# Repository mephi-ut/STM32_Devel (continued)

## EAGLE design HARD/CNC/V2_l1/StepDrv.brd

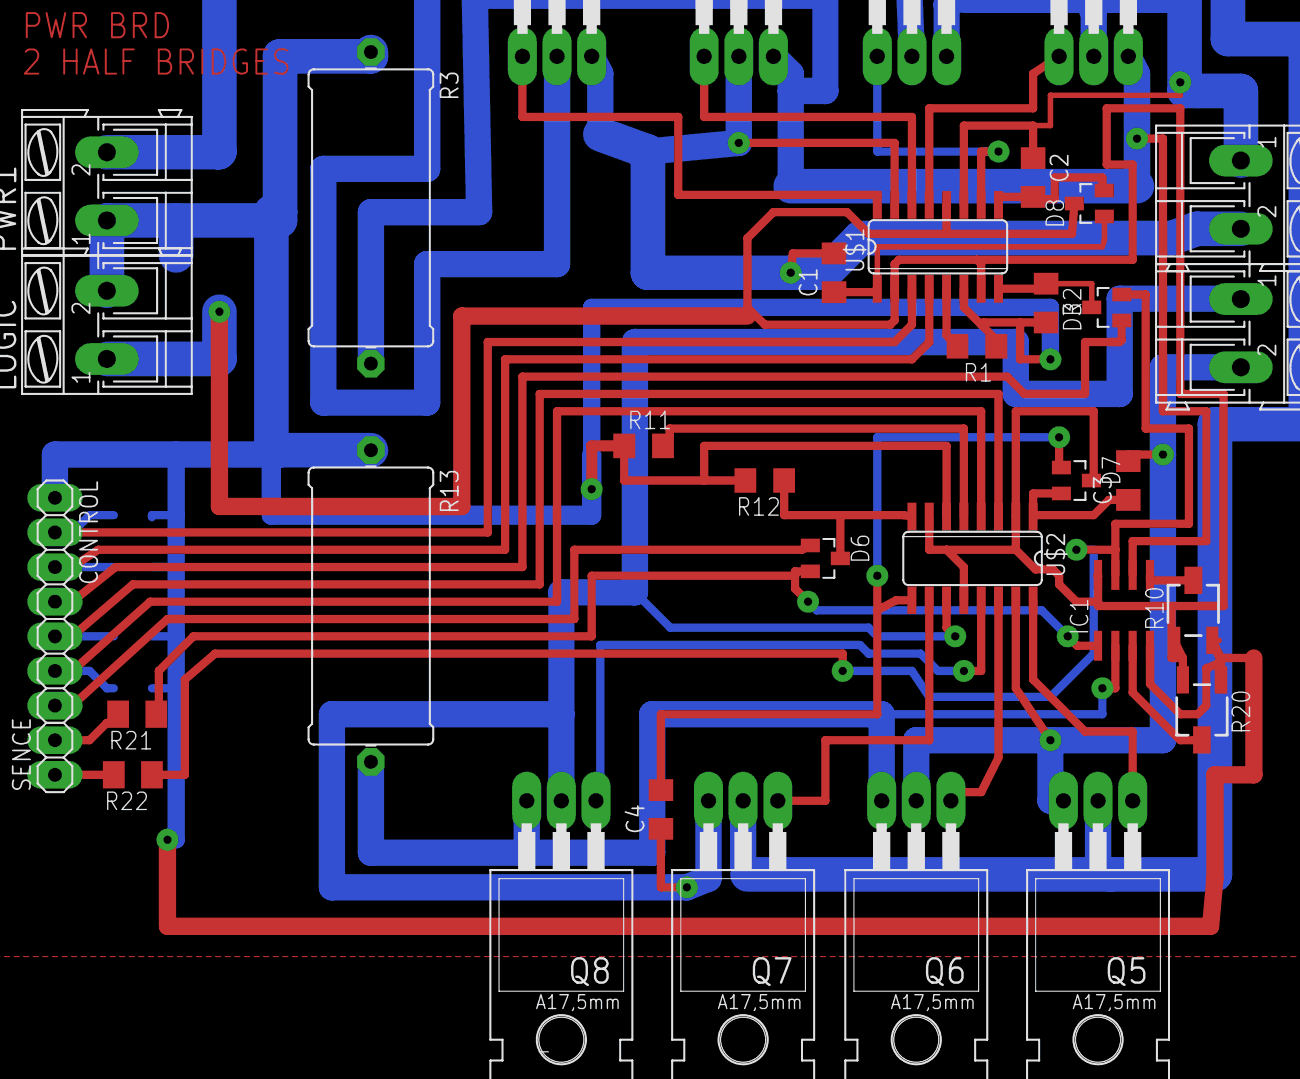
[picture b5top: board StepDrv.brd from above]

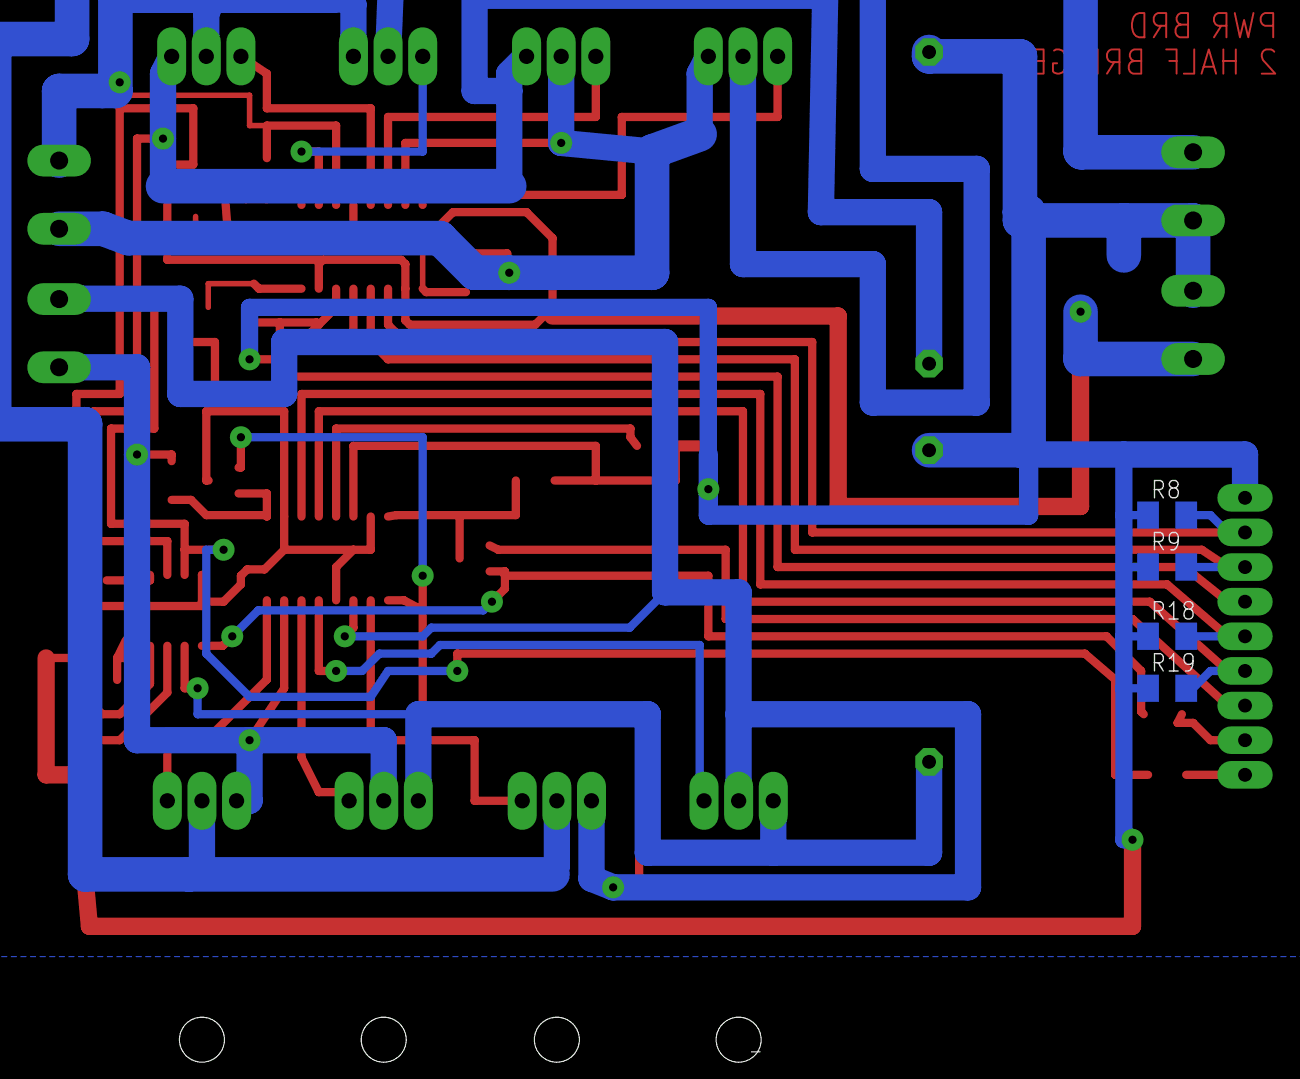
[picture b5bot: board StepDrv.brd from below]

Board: 2 copper layers, 39 parts (4 on the bottom side), 37 nets.

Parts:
AO1: OUT; AK300/2
BO: OUT; AK300/2
C1, C2, C3, C4: 2.2uF; C1206
CONTROL: 1X07
D3, D6: HSMS-2854; SOT23
D7, D8: HSMS-2853; SOT23
IC1: LM358D; SO08
LOGIC: 12V; AK300/2
PWR1: AK300/2
Q1, Q2, Q3, Q4, Q5, Q6, Q7, Q8: IRFZ48Z; TO220BH
R1, R2, R11, R12: R1206
R3, R13: 0922/22
R8, R9, R18, R19, R21, R22: M1206
R10, R20: 3223G
SENCE: 1X02
U$1, U$2: HIP4082IBZT; SO16

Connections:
unnamed: C2.2, D8.2, U$1.9
unnamed: D3.3, R2.1, U$1.8
unnamed: C1.1, D8.1, U$1.1
unnamed: BO.2, C1.2, Q1.S, Q2.D, U$1.15
unnamed: CONTROL.4, D3.1
unnamed: R1.2, U$1.5
unnamed: R21.2, SENCE.2
unnamed: BO.1, C2.1, Q3.S, Q4.D, U$1.11
unnamed: CONTROL.3, R9.2, U$1.4
unnamed: CONTROL.2, R8.2, U$1.3
unnamed: IC1.6, Q2.S, Q4.S, R3.2
unnamed: Q1.G, U$1.16
unnamed: Q2.G, U$1.14
unnamed: Q3.G, U$1.10
unnamed: Q4.G, U$1.13
unnamed: D3.2, IC1.7, R22.1
unnamed: IC1.5, R10.2
unnamed: C4.2, D7.1, U$2.9
unnamed: C3.1, D7.2, U$2.1
unnamed: AO1.2, C3.2, Q5.S, Q6.D, U$2.15
unnamed: CONTROL.7, D6.1
unnamed: R11.2, U$2.5
unnamed: AO1.1, C4.1, Q7.S, Q8.D, U$2.11
unnamed: IC1.2, Q6.S, Q8.S, R13.2
unnamed: Q5.G, U$2.16
unnamed: Q6.G, U$2.14
unnamed: Q7.G, U$2.10
unnamed: Q8.G, U$2.13
unnamed: CONTROL.6, R19.2, U$2.4
unnamed: CONTROL.5, R18.2, U$2.3
unnamed: R22.2, SENCE.1
unnamed: D6.3, R12.1, U$2.8
unnamed: D6.2, IC1.1, R21.1
unnamed: IC1.3, R20.2
unnamed: PWR1.2, Q1.D, Q3.D, Q5.D, Q7.D
unnamed: CONTROL.1, IC1.4, LOGIC.2, PWR1.1, R1.1, R2.2, R3.1, R8.1, R9.1, R10.3, R11.1, R12.2, R13.1, R18.1, R19.1, R20.1, U$1.6, U$2.6
unnamed: D7.3, D8.3, IC1.8, LOGIC.1, R10.1, R20.3, U$1.2, U$1.7, U$1.12, U$2.2, U$2.7, U$2.12
